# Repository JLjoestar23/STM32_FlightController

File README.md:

# STM32_FlightController
PCB, software, firmware, and other files related to a custom made STM32-based flight controller.

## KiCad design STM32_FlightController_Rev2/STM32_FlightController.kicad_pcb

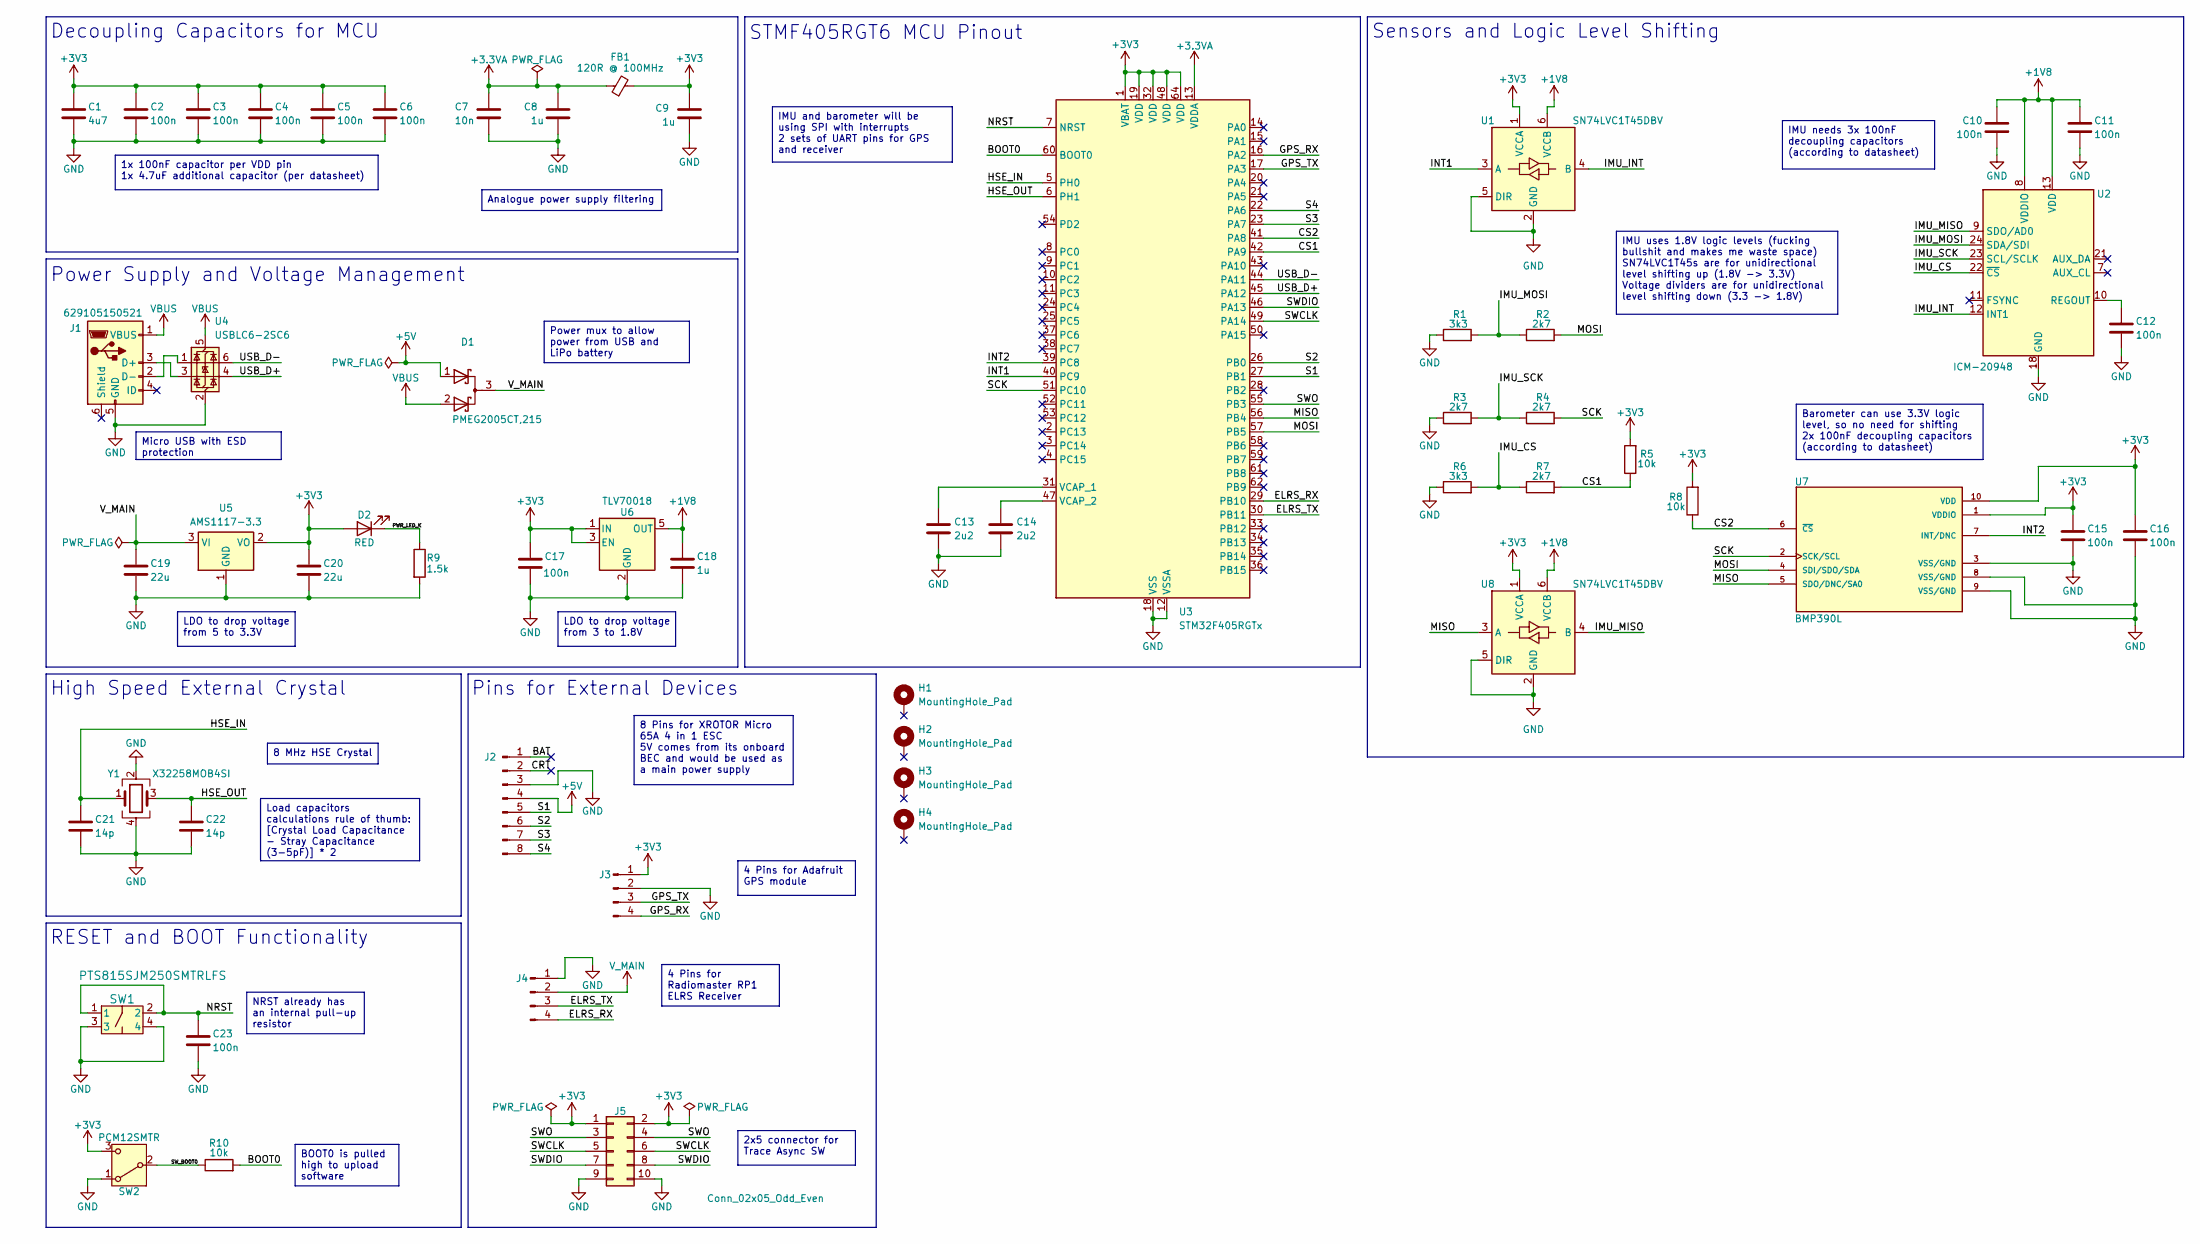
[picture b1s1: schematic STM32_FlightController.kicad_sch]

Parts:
C1: 4u7; C_0603_1608Metric
C2, C3, C4, C5, C6, C10, C11, C12, C15, C16, C23: 100n; C_0402_1005Metric
C7: 10n; C_0402_1005Metric
C8, C9: 1u; C_0402_1005Metric
C13, C14: 2u2; C_0603_1608Metric
C17: 100n; C_0603_1608Metric
C18: 1u; C_0603_1608Metric
C19, C20: 22u; C_0805_2012Metric
C21, C22: 14p; C_0402_1005Metric
D1: PMEG2005CT,215; SOT-23
D2: RED; LED_0603_1608Metric
FB1: 120R @ 100MHz; L_0603_1608Metric
H1, H2, H3, H4: MountingHole_Pad; MountingHole_4mm_Pad
J1: 629105150521; USB_Micro-B_Wuerth_629105150521
J2: JST_SH_SM08B-SRSS-TB_1x08-1MP_P1.00mm_Horizontal
J3, J4: JST_SH_SM04B-SRSS-TB_1x04-1MP_P1.00mm_Horizontal
J5: Conn_02x05_Odd_Even; PinHeader_2x05_P1.27mm_Vertical
R1, R6: 3k3; R_0402_1005Metric
R2, R3, R4, R7: 2k7; R_0402_1005Metric
R5, R8, R10: 10k; R_0402_1005Metric
R9: 1.5k; R_0402_1005Metric
SW1: PTS815SJM250SMTRLFS; SW4_PTS815 SJM 250 SMTR LFS_CNK
SW2: PCM12SMTR; SW_SPDT_PCM12
U1, U8: SN74LVC1T45DBV; SOT-23-6
U2: ICM-20948; InvenSense_QFN-24_3x3mm_P0.4mm
U3: STM32F405RGTx; LQFP-64_10x10mm_P0.5mm
U4: USBLC6-2SC6; SOT-23-6
U5: AMS1117-3.3; SOT-223-3_TabPin2
U6: TLV70018; SOT-23-5
U7: BMP390L; PARTREV 1.7
Y1: X32258MOB4SI; Crystal_SMD_3225-4Pin_3.2x2.5mm

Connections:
+1V8: C10.1, C11.1, C18.1, U1.6 (VCCB), U2.8 (VDDIO), U2.13 (VDD), U6.5 (OUT), U8.6 (VCCB)
+3.3VA: C7.1, C8.1, FB1.1, U3.13 (VDDA)
+3V3: C1.1, C2.1, C3.1, C4.1, C5.1, C6.1, C9.1, C15.1, C16.1, C17.1, C20.1, D2.2 (A), FB1.2, J3.1, J5.1, J5.2, R5.2, R8.2, SW2.3 (C), U1.1 (VCCA), U3.1 (VBAT), U3.19 (VDD), U3.32 (VDD), U3.48 (VDD), U3.64 (VDD), U5.2 (VO), U6.1 (IN), U6.3 (EN), U7.1 (VDDIO), U7.10 (VDD), U8.1 (VCCA)
+5V: D1.1 (A), J2.4
/BAT: J2.1
/BOOT0: R10.2, U3.60 (BOOT0)
/CRT: J2.2
/CS1: R5.1, R7.2, U3.42 (PA9)
/CS2: R8.1, U3.41 (PA8), U7.6 (~CS)
/ELRS_RX: J4.4, U3.29 (PB10)
/ELRS_TX: J4.3, U3.30 (PB11)
/GPS_RX: J3.4, U3.16 (PA2)
/GPS_TX: J3.3, U3.17 (PA3)
/HSE_IN: C21.1, U3.5 (PH0), Y1.1
/HSE_OUT: C22.1, U3.6 (PH1), Y1.3
/IMU_CS: R6.2, R7.1, U2.22 (~CS)
/IMU_INT: U1.4 (B), U2.12 (INT1)
/IMU_MISO: U2.9 (SDO/AD0), U8.4 (B)
/IMU_MOSI: R1.2, R2.1, U2.24 (SDA/SDI)
/IMU_SCK: R3.2, R4.1, U2.23 (SCL/SCLK)
/INT1: U1.3 (A), U3.40 (PC9)
/INT2: U3.39 (PC8), U7.7 (INT/DNC)
/MISO: U3.56 (PB4), U7.5 (SDO/DNC/SA0), U8.3 (A)
/MOSI: R2.2, U3.57 (PB5), U7.4 (SDI/SDO/SDA)
/NRST: C23.1, SW1.1, SW1.2, U3.7 (NRST)
/PWR_LED_K: D2.1 (K), R9.1
/S1: J2.5, U3.27 (PB1)
/S2: J2.6, U3.26 (PB0)
/S3: J2.7, U3.23 (PA7)
/S4: J2.8, U3.22 (PA6)
/SCK: R4.2, U3.51 (PC10), U7.2 (SCK/SCL)
/SWCLK: J5.5, J5.6, U3.49 (PA14)
/SWDIO: J5.7, J5.8, U3.46 (PA13)
/SWO: J5.3, J5.4, U3.55 (PB3)
/SW_BOOT0: R10.1, SW2.2 (B)
/USB_D+: U3.45 (PA12), U4.4 (I/O2)
/USB_D-: U3.44 (PA11), U4.6 (I/O1)
GND: C1.2, C2.2, C3.2, C4.2, C5.2, C6.2, C7.2, C8.2, C9.2, C10.2, C11.2, C12.2, C13.2, C14.2, C15.2, C16.2, C17.2, C18.2, C19.2, C20.2, C21.2, C22.2, C23.2, J1.5 (GND), J2.3, J3.2, J4.1, J5.9, J5.10, R1.1, R3.1, R6.1, R9.2, SW1.3, SW1.4, SW2.1 (A), U1.2 (GND), U1.5 (DIR), U2.18 (GND), U2.20 (GND), U3.12 (VSSA), U3.18 (VSS), U3.63 (VSS), U4.2 (GND), U5.1 (GND), U6.2 (GND), U7.3 (VSS/GND), U7.8 (VSS/GND), U7.9 (VSS/GND), U8.2 (GND), U8.5 (DIR), Y1.2, Y1.4
unnamed: J1.3 (D+), U4.3 (I/O2)
unnamed: J1.2 (D-), U4.1 (I/O1)
unnamed: C12.1, U2.10 (REGOUT)
unnamed: C13.1, U3.31 (VCAP_1)
unnamed: C14.1, U3.47 (VCAP_2)
VBUS: D1.2 (A), J1.1 (VBUS), U4.5 (VBUS)
V_MAIN: C19.1, D1.3 (K), J4.2, U5.3 (VI)

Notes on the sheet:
Pins for External Devices
STMF405RGT6 MCU Pinout
High Speed External Crystal
Power Supply and Voltage Management
RESET and BOOT Functionality
Decoupling Capacitors for MCU
Sensors and Logic Level Shifting
4 Pins for Radiomaster RP1 ELRS Receiver
NRST already has an internal pull-up resistor
4 Pins for Adafruit GPS module
IMU needs 3x 100nF decoupling capacitors (according to datasheet)
Power mux to allow power from USB and LiPo battery
Barometer can use 3.3V logic level, so no need for shifting 2x 100nF decoupling capacitors (according to datasheet)
LDO to drop voltage from 5 to 3.3V
Load capacitors calculations rule of thumb: [Crystal Load Capacitance - Stray Capacitance (3-5pF)] * 2
BOOT0 is pulled high to upload software
LDO to drop voltage from 3 to 1.8V
IMU and barometer will be using SPI with interrupts 2 sets of UART pins for GPS and receiver
8 MHz HSE Crystal
8 Pins for XROTOR Micro 65A 4 in 1 ESC 5V comes from its onboard BEC and would be used as a main power supply
1x 100nF capacitor per VDD pin 1x 4.7uF additional capacitor (per datasheet)
2x5 connector for Trace Async SW
IMU uses 1.8V logic levels (fucking bullshit and makes me waste space) SN74LVC1T45s are for unidirectional level shifting up (1.8V -> 3.3V) Voltage dividers are for unidirectional level shifting down (3.3 -> 1.8V)
Micro USB with ESD protection
Analogue power supply filtering

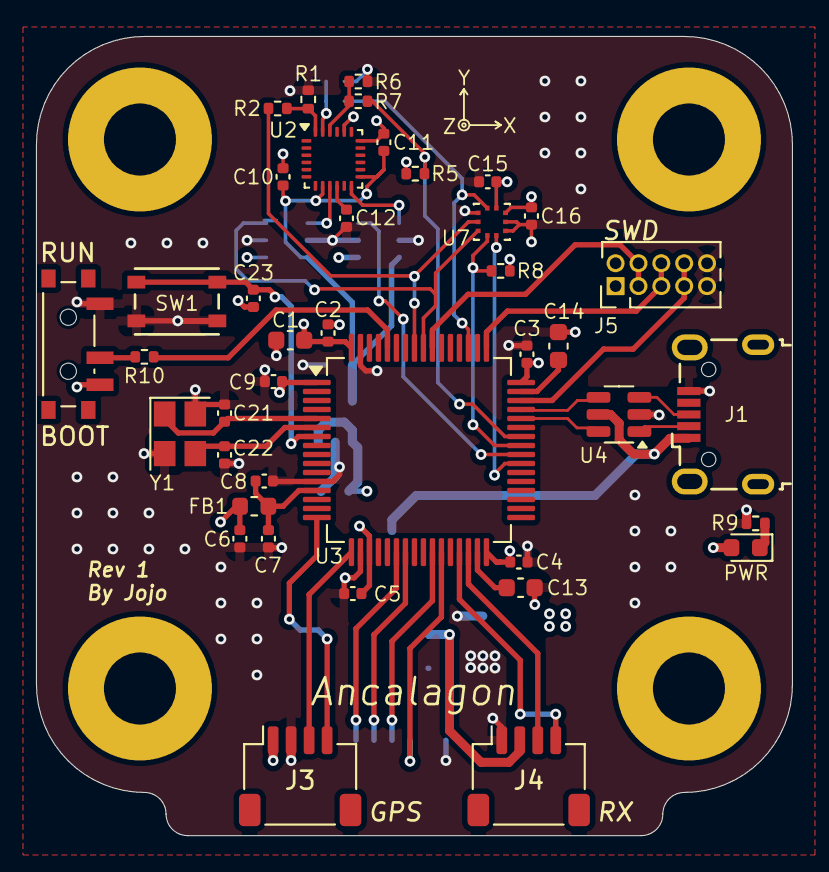
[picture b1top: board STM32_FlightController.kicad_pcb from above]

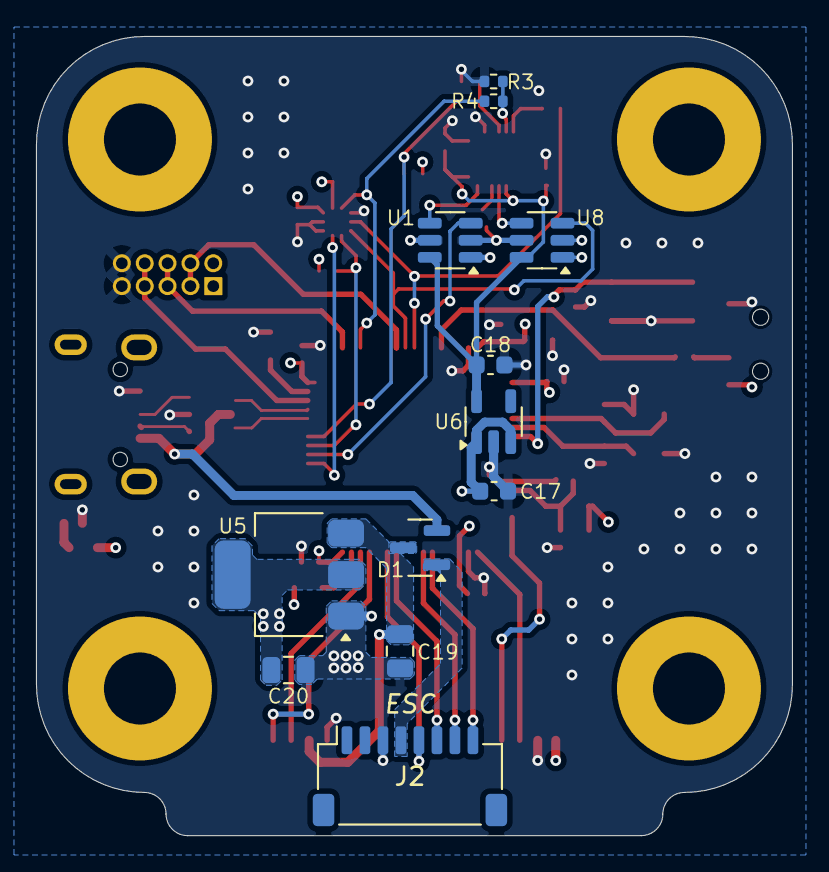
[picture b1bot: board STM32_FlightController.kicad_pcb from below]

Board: 4 copper layers, 42.0 x 44.4 mm, 56 parts (12 on the bottom side), 43 nets.

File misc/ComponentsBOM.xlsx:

PART NUMBER | PART NAME | DESCRIPTION | QUANTITY | SUPPLIER / MANUFACTURER | UNIT COST | TOTAL PART COST | PURCHASED
C1 | GRM188C71A475KE11D | 4.7uF 0603 SMD Ceramic Capacitor | 10 | https://www.digikey.com/en/products/detail/murata-electronic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 | 0.13 | 1.3 | 1
C2,C3,C4,C5,C6,C10,C11,C12,C15,C16,C17,C23 | CC0402KRX7R7BB104 | 100nF 0402 SMD Ceramic Capacitor | 60 | https://www.digikey.com/en/products/detail/yageo/CC0402KRX7R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 | 1.43E-2 | 0.85799999999999998 | 1
C7 | CC0402KRX7R9BB103 | 10nF 0402 SMD Ceramic Capacitor | 10 | https://www.digikey.com/en/products/detail/yageo/CC0402KRX7R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 | 8.9999999999999993E-3 | 0.09 | 1
C8,C9,C18 | CC0402KRX5R5BB105 | 1uF 0402 SMD Ceramic Capacitor | 30 | https://www.digikey.com/en/products/detail/yageo/CC0402KRX5R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 | 5.3999999999999999E-2 | 1.6199999999999999 | 1
C13,C14 | GRM188R71A225KE15J | 2.2uF 0603 SMD Ceramic Capacitor | 20 | https://www.digikey.com/en/products/detail/murata-electronic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 | 8.5000000000000006E-2 | 1.7000000000000002 | 1
C19,C20 | GRM21BC81C226ME44L | 22uF 0805 SMD Ceramic Capacitor | 10 | https://www.digikey.com/en/products/detail/murata-electronic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 | 0.27800000000000002 | 2.7800000000000002 | 1
C21,C22 | GJM1555C1H140GB01D | 14pF 0402 SMD Ceramic Capacitor | 20 | https://www.digikey.com/en/products/detail/murata-electronic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 | 6.9000000000000006E-2 | 1.3800000000000001 | 1
D1 | PMEG2005CT,215 | Diode Array/Power Mux | 5 | https://www.digikey.com/en/products/detail/nexperia-usa-inc/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 | 0.105 | 0.52500000000000002 | 1
D2 | LTST-C193KRKT-5A | RED LED | 5 | https://www.digikey.com/en/products/detail/liteon/LTST-C193K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 | 0.13600000000000001 | 0.68 | 1
FB1 | BLM18PG121SN1D | 100Ω @ 120MHz 0603 SMD Ferrite Bead | 10 | https://www.digikey.com/en/products/detail/murata-electronic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 | 0.06 | 0.6 | 1
J1 | USB Micro-B Wuerth 629105150521 | Micro USB Connector | 2 | https://www.digikey.com/en/products/detail/w%C3%BCrth-elektr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 | 2.21 | 4.42 | 1
J2 | SM08B-SRSS-TB(LF)(SN) | 1x8 Horizontal SMT JST-SH connector | 2 | https://www.digikey.com/en/products/detail/jst-sales-america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 | 0.78 | 1.56 | 1
J3,J4 | SM04B-SRSS-TB(LF)(SN) | 1x4 Horizontal SMT JST-SH connector | 8 | https://www.chip1stop.com/USA/en/products/J.S.T.-MFG/SM04B-S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 | 0.58399999999999996 | 4.6719999999999997 | 1
J5 | GRPB052VWVN-RC | 2x5 Vertical 1.27mm Pin Header | 2 | https://www.digikey.com/en/products/detail/sullins-connector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 | 0.61 | 1.22 | 1
R1,R6 | RC0402JR-073K3L | 3.3kΩ 0402 SMD Resistor | 20 | https://www.digikey.com/en/products/detail/yageo/RC0402JR-07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 | 7.0000000000000001E-3 | 0.14000000000000001 | 1
R2,R3,R4,R7 | RC0402FR-072K7L | 2.7kΩ 0402 SMD Resistor | 40 | https://www.digikey.com/en/products/detail/yageo/RC0402FR-07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 | 8.0000000000000002E-3 | 0.32 | 1
R5,R8,R10 | RC0402JR-0710KL | 10kΩ 0402 SMD Resistor | 30 | https://www.digikey.com/en/products/detail/yageo/RC0402JR-07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 | 7.0000000000000001E-3 | 0.21 | 1
R9 | RC0402JR-071K5L | 1.5kΩ 0402 SMD Resistor | 10 | https://www.digikey.com/en/products/detail/yageo/RC0402JR-07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 | 7.0000000000000001E-3 | 7.0000000000000007E-2 | 1
SW1 | PTS815SJM250SMTRLFS | Tactile Switch Button | 5 | https://www.digikey.com/en/products/detail/c-k/PTS815SJM250S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 | 0.22 | 1.1000000000000001 | 1
SW2 | PCM12SMTR | Tactile 2 Way Switch | 2 | https://www.digikey.com/en/products/detail/c-k/PCM12SMTR/1640112 | 1.1399999999999999 | 2.2799999999999998 | 1
U1,U8 | SN74LVC1T45DBVR | 3.3V - 1.8V Logic Level Shifter | 10 | https://www.digikey.com/en/products/detail/texas-instruments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 | 0.29099999999999998 | 2.9099999999999997 | 1
U2 | ICM-20948 | 9 Axis IMU | 2 | https://www.digikey.com/en/products/detail/tdk-invensense/IC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 | 6.78 | 13.56 | 1
U3 | STM32F405RGT6 | Microcontroller Unit | 2 | https://www.digikey.com/en/products/detail/stmicroelectronic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 | 11.14 | 22.28 | 1
U4 | USBLC6-2SC6 | ESD Protection for USB | 5 | https://www.digikey.com/en/products/detail/stmicroelectronic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 | 0.36 | 1.7999999999999998 | 1
U5 | AMS1117-3.3 | 5V - 3.3V Low-Dropout Regulator | 5 | https://www.digikey.com/en/products/detail/evvo/AMS1117-3-3/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 | 0.27 | 1.35 | 1
U6 | TLV70018 | 3.3V - 1.8V Low-Dropout Regulator | 5 | https://www.digikey.com/en/products/detail/texas-instruments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 | 0.2 | 1 | 1
U7 | BMP390 | Barometric Pressure Sensor | 2 | https://www.digikey.com/en/products/detail/bosch-sensortec/B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 | 3.15 | 6.3 | 1
Y1 | X32258MOB4SI | 8MHz Crystal | 5 | https://lcsc.com/product-detail/Crystals_Yangxing-Tech-X3225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 | 0.16489999999999999 | 0.82450000000000001 | 1
 |  | TOTAL PARTS | 337 |  | TOTAL | 77.549499999999995

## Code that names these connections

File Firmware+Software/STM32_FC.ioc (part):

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Mcu.Name=STM32F405RGTx
Mcu.Package=LQFP64
Mcu.UserName=STM32F405RGTx
PA11.Mode=Device_Only
PA11.Signal=USB_OTG_FS_DM
PA12.Mode=Device_Only
PA12.Signal=USB_OTG_FS_DP
PA13.Mode=Trace_Asynchronous_SW
PA13.Signal=SYS_JTMS-SWDIO
PA14.Mode=Trace_Asynchronous_SW
PA14.Signal=SYS_JTCK-SWCLK
PA2.GPIOParameters=GPIO_Label
PA2.GPIO_Label=USART2_TX (GPS_RX)
PA2.Mode=Asynchronous
PA2.Signal=USART2_TX
PA3.GPIOParameters=GPIO_Label
PA3.GPIO_Label=USART2_RX (GPS_TX)
PA3.Mode=Asynchronous
PA3.Signal=USART2_RX
PA6.Signal=S_TIM3_CH1
PA7.Signal=S_TIM3_CH2
PA8.GPIOParameters=GPIO_Label
PA8.GPIO_Label=NCS2
PA8.Signal=GPIO_Output
PA9.GPIOParameters=GPIO_Label
PA9.GPIO_Label=NCS1
PA9.Signal=GPIO_Output
PB0.Signal=S_TIM3_CH3
PB1.Signal=S_TIM3_CH4
PB10.GPIOParameters=GPIO_Label
PB10.GPIO_Label=USART3_TX (RX_RX)
PB10.Mode=Asynchronous
PB10.Signal=USART3_TX
PB11.GPIOParameters=GPIO_Label
PB11.GPIO_Label=USART3_RX (RX_TX)
PB11.Mode=Asynchronous
PB11.Signal=USART3_RX
PB3.Mode=Trace_Asynchronous_SW
PB3.Signal=SYS_JTDO-SWO
PB4.Mode=Full_Duplex_Master
PB4.Signal=SPI3_MISO
PB5.Mode=Full_Duplex_Master
PB5.Signal=SPI3_MOSI
PC10.Mode=Full_Duplex_Master
PC10.Signal=SPI3_SCK
PC8.GPIOParameters=GPIO_Label
PC8.GPIO_Label=INT2
PC8.Signal=GPXTI8
PC9.GPIOParameters=GPIO_Label
PC9.GPIO_Label=INT1
PC9.Signal=GPXTI9
PH0-OSC_IN.Mode=HSE-External-Oscillator
PH0-OSC_IN.Signal=RCC_OSC_IN
PH1-OSC_OUT.Mode=HSE-External-Oscillator
PH1-OSC_OUT.Signal=RCC_OSC_OUT
RCC.HSE_VALUE=8000000
RCC.SYSCLKFreq_VALUE=168000000
RCC.SYSCLKSource=RCC_SYSCLKSOURCE_PLLCLK
board=custom

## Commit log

2025-05-25 initial commit of PCB related files
2025-05-28 added firmware framework, some PCB modifications
2025-05-28 routing and layout changes
2025-05-28 corrected BMP390 schematic wiring and layout, among other corrections
2025-05-28 fixed respective RX and TX wirings
2025-05-29 correcting majority of via placements
2025-05-31 suggested fixes
2025-06-01 re-speccing the power mux to PMEG2005CT,215 rated for 500 mA
2025-06-03 replaced transistors with level shifter ICs
    transistors appeared to switch to slowly for SPI, ICs seemed like they would be fast enough
    required significant rerouting of SPI traces from sensors
2025-06-04 90 ohm impedance matching for USB traces
2025-06-04 added some datasheets, planning to use JST ZH
2025-06-05 replaced pads with corresponding JST-SH connectors
2025-06-05 adjusted mounting hole positions to 30.5mm apart
2025-06-06 various minor adjustments for positioning
2025-06-09 finalizing components, adjusting some positioning
2025-06-09 replaced mounting holes with padded ones
2025-06-09 minor positioning changes
2025-06-10 cubeIDE code generation/setup
2025-06-10 swapped 5V and GND on the ELRS receiver connector
2025-06-10 added top, bottom ground planes w/ stitching
2025-06-10 final edits, passed DRC
2025-06-11 added manufacturing related files
2025-06-12 added general BOM
2025-06-12 added some draw rule areas for GND planes
2025-06-13 aesthetics changes
2025-06-13 re-did manufacturing files
2025-06-13 still trying to resolve merge conflict
2025-06-13 re-organizing manufacturing related files
2025-06-13 more re-organization
2025-06-15 added manufacturing stencils, some more organization
2025-06-15 updated BOM
2025-06-15 began development of SPI driver
2025-06-17 further SPI driver development
2025-06-17 creating SPI simultaneous read-write function
2025-06-17 polishing SPI driver code
2025-06-17 minor SPI changes
2025-06-22 developing IMU drivers
2025-07-08 backup file updates
2025-07-08 edits to manufacturing stencils
2025-07-08 further development to IMU driver
2025-07-14 minor adjustment to pointer usage with read/write functions
2025-07-14 added useful comments regarding registers, re-wrote read_mag_vec()
2025-07-15 changed dataframe format to 8 bits
2025-07-15 improved in-line documentation
2025-07-25 started development of IMU calibration functionality
2025-07-26 implemented gyroscope calibration function
2025-07-26 auto preference changes
2025-07-27 implemented accel calibration function
2025-07-28 correct PCB traces regarding TIM pins
2025-07-28 code changed with TIM3 channel configurations
2025-07-28 remade the manufacturing folder
2025-07-29 corrections to the IMU driver header file
2025-07-29 added missing read/write compass function definitions
2025-07-29 implemented IMU driver using SPI HAL as an alternative
2025-07-29 preference and language changes
2025-07-30 fixed incorrect usage of pointers in IMU read/write functions
2025-08-02 re-implemented read/write functions
2025-08-02 added burst write capabilities for bias comp
2025-08-02 preference changes
2025-08-06 configured USART3 for DMA
2025-08-13 initial implementation to parse ELRS packets
2025-08-16 added comments to elrs.c
2025-08-16 Update language settings
